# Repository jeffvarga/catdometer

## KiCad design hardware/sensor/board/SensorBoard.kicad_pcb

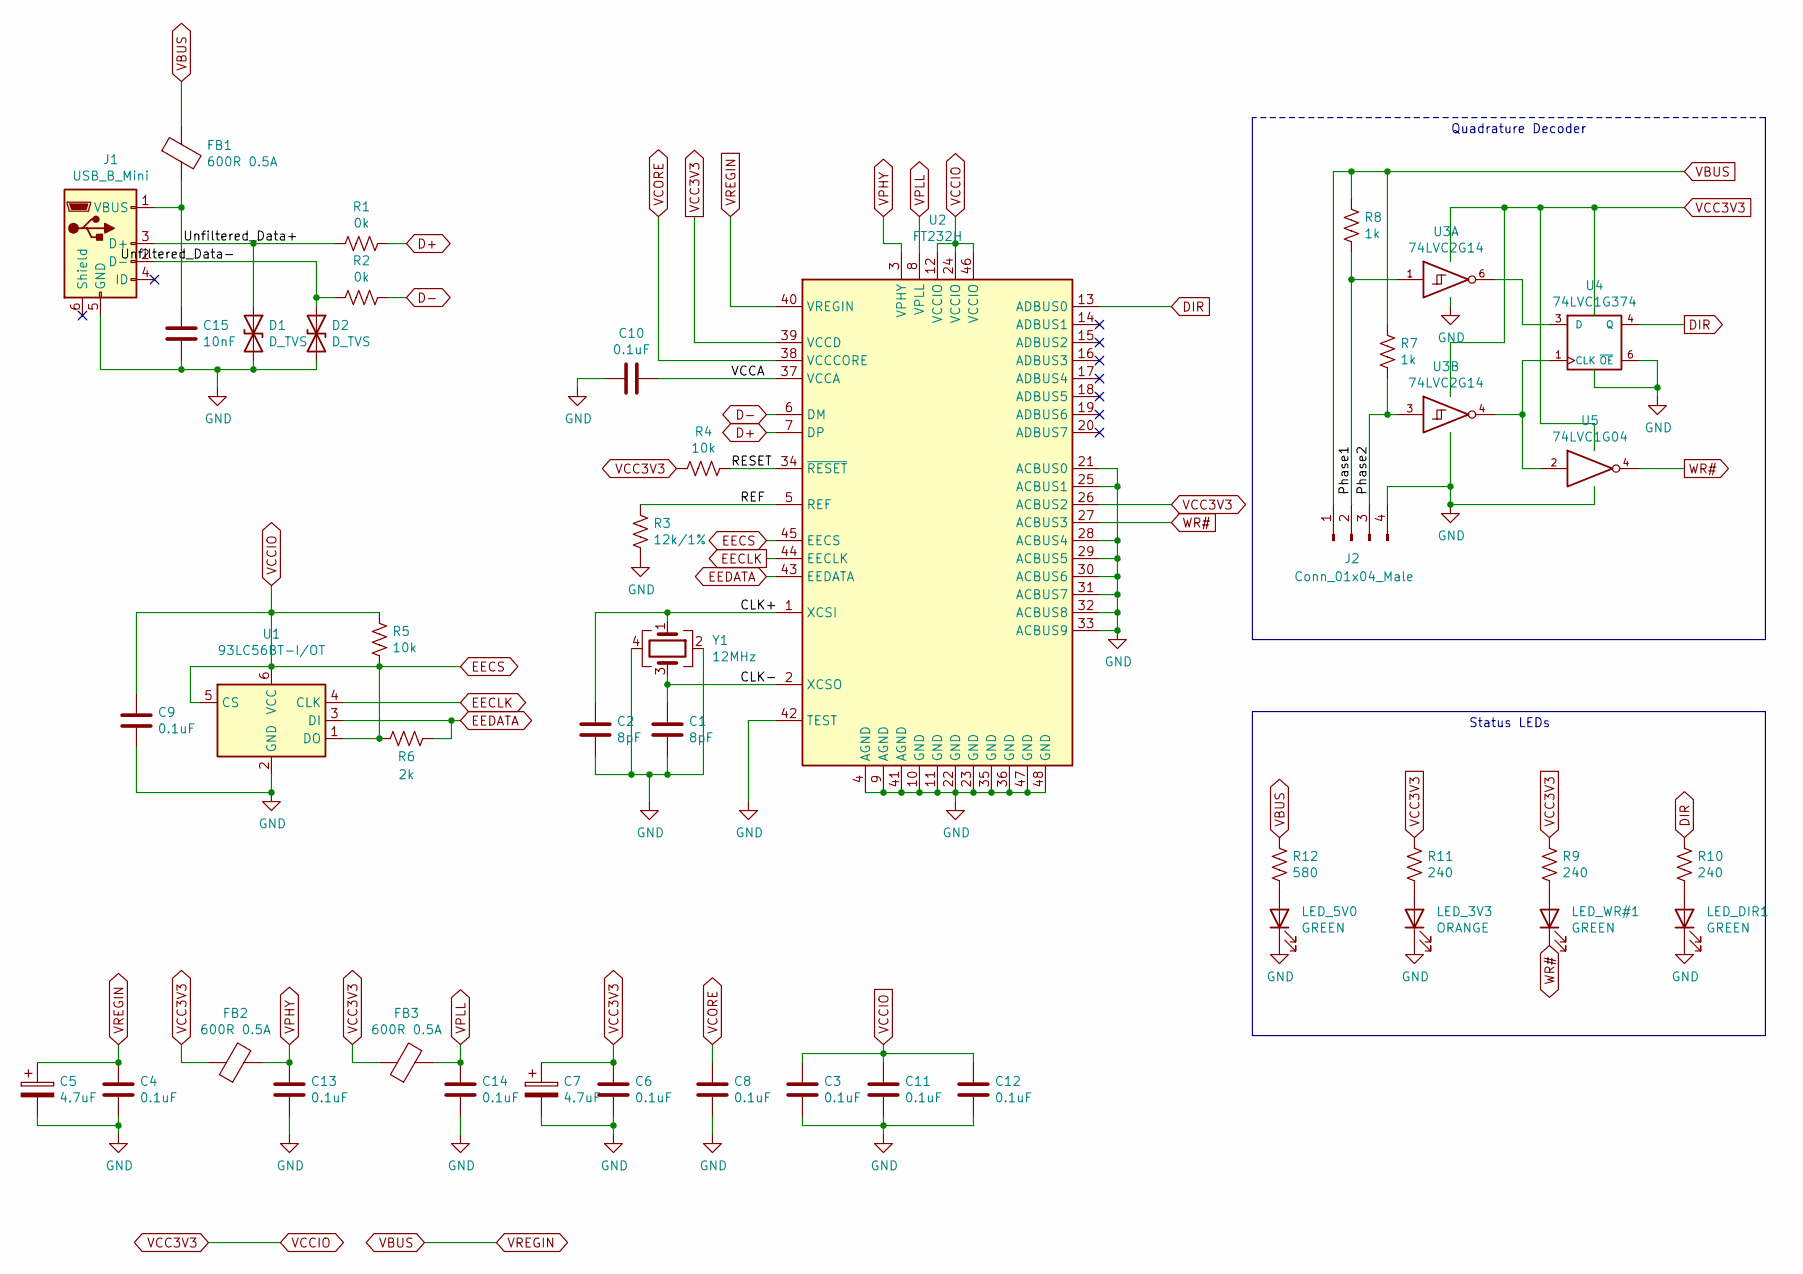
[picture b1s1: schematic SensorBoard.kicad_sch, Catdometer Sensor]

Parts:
C1, C2: 8pF; C_0603_1608Metric; Digikey Item CL10C270JB81PNC
C3, C4, C6, C8, C9, C10, C11, C12, C13, C14: 0.1uF; C_0603_1608Metric; Digikey Item CL10A104KA8NNNC
C5, C7: 4.7uF; C_0603_1608Metric; Digikey Item CL10A475KP8NNNC‎
C15: 10nF; C_0603_1608Metric; Digikey Item CL10B103KB8NNNC
D1, D2: D_TVS; D_0603_1608Metric; Digikey Item PGB1010603MR‎
FB1, FB2, FB3: 600R 0.5A; L_0603_1608Metric; Digikey Item BLM18AG601SN1D‎
J1: USB_B_Mini; USB_Mini-B_Wuerth_65100516121_Horizontal; Digikey Item ‎65100516121‎
J2: Conn_01x04_Male; PinHeader_1x04_P2.54mm_Vertical
LED_3V3: ORANGE; LED_0603_1608Metric
LED_5V0: GREEN; LED_0603_1608Metric
LED_DIR1: GREEN; LED_0603_1608Metric
LED_WR#1: GREEN; LED_0603_1608Metric
R1, R2: 0k; R_0603_1608Metric; Digikey Item ERJ-3GEY0R00V
R3: 12k/1%; R_0603_1608Metric; Digikey Item ERJ-PA3F1202V
R4, R5: 10k; R_0603_1608Metric; Digikey Item ERJ-PA3J103V
R6: 2k; R_0603_1608Metric; Digikey Item ‎ERJ-PA3J202V‎
R7, R8: 1k; R_0603_1608Metric; Digikey Item ERJ-PA3J102V
R9, R10: 240; R_0603_1608Metric; Digikey Item ERJ-PA3J102V
R11: 240; R_0603_1608Metric
R12: 580; R_0603_1608Metric
U1: 93LC56BT-I/OT; SOT-23-6
U2: FT232H; LQFP-48_7x7mm_P0.5mm
U3: 74LVC2G14; SOT-23-6
U4: 74LVC1G374; SOT-23-6
U5: 74LVC1G04; SOT-23-5
Y1: 12MHz; Crystal_SMD_2520-4Pin_2.5x2.0mm; Digikey Item ABM10-167-12.000MHZ-T3

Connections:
/CLK+: C2.1, U2.1 (XCSI), Y1.1
/CLK-: C1.1, U2.2 (XCSO), Y1.3
/Phase1: J2.2, R8.2, U3.1
/Phase2: J2.3, R7.2, U3.3
/REF: R3.1, U2.5 (REF)
/RESET: R4.1, U2.34 (~RESET)
/Unfiltered_Data+: D1.1 (A1), J1.3 (D+), R1.2
/Unfiltered_Data-: D2.1 (A1), J1.2 (D-), R2.2
/VCCA: C10.1, U2.37 (VCCA)
D+: R1.1, U2.7 (DP)
D-: R2.1, U2.6 (DM)
DIR: R10.1, U2.13 (ADBUS0), U4.4 (Q)
EECLK: U1.4 (CLK), U2.44 (EECLK)
EEDATA: R6.1, U1.3 (DI), U2.43 (EEDATA)
GND: C1.2, C2.2, C3.2, C4.2, C5.2, C6.2, C7.2, C8.2, C9.2, C10.2, C11.2, C12.2, C13.2, C14.2, C15.2, D1.2 (A2), D2.2 (A2), J1.5 (GND), J2.4, LED_3V3.1 (K), LED_5V0.1 (K), LED_DIR1.1 (K), R3.2, U1.2 (GND), U2.4 (AGND), U2.9 (AGND), U2.10 (GND), U2.11 (GND), U2.21 (ACBUS0), U2.22 (GND), U2.23 (GND), U2.25 (ACBUS1), U2.28 (ACBUS4), U2.29 (ACBUS5), U2.30 (ACBUS6), U2.31 (ACBUS7), U2.32 (ACBUS8), U2.33 (ACBUS9), U2.35 (GND), U2.36 (GND), U2.41 (AGND), U2.42 (TEST), U2.47 (GND), U2.48 (GND), U3.2 (GND), U4.2 (GND), U4.6 (~OE), U5.3 (GND), Y1.2, Y1.4
unnamed: C15.1, FB1.2, J1.1 (VBUS)
unnamed: LED_3V3.2 (A), R11.2
unnamed: LED_5V0.2 (A), R12.2
unnamed: LED_DIR1.2 (A), R10.2
unnamed: LED_WR#1.2 (A), R9.2
unnamed: U3.4, U4.1 (CLK), U5.2
unnamed: U3.6, U4.3 (D)
VBUS: C4.1, C5.1, FB1.1, J2.1, R7.1, R8.1, R12.1, U2.40 (VREGIN)
VCORE: C8.1, U2.38 (VCCCORE)
VPHY: C13.1, FB2.2, U2.3 (VPHY)
VPLL: C14.1, FB3.2, U2.8 (VPLL)
WR#: LED_WR#1.1 (K), U2.27 (ACBUS3), U5.4

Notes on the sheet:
Status LEDs
Quadrature Decoder

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
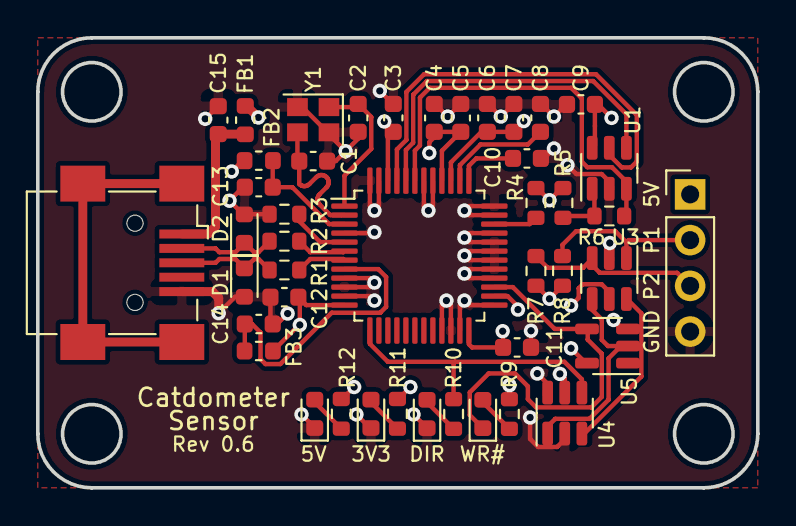
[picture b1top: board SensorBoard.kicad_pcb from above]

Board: 4 copper layers, 40.0 x 25.0 mm, 44 parts (0 on the bottom side), 30 nets.

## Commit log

2020-08-09 Create LICENSE
2020-08-09 Moving source files
2020-08-09 Refactoring code into modules
2020-08-11 Major refactor of libraries, arguing with python import semantics.
2020-08-11 Uploading correct version of service with path to real script
2020-08-28 Hey, I'm learning Tk! Using the proper packers for the job and reducing complexity of layout.
2020-08-28 Abstracting the speedometer circle drawing code into a base and derived classes to change the look.
2020-09-01 Change the default inactive tick style to dark gray
2020-09-01 Encapsulate some anonymous tuples in collections.namedtuple wrappers. Clean up some of the math for the DottedSpeedometer.
2020-09-02 Missing line break at end of file
2020-09-02 Moar colors
2020-09-02 Updating DottedSpeedometer to use named colors
2020-09-02 Refactoring Rect, Point into its own Geometry module. Adding a few helper functions to Rect like width/height.
2020-09-02 Rename of Speedometer (Base, Dashed, Dotted) to Gauge to reduce confusion and better represent what the class is doing.
2020-09-03 requirements.txt
2020-09-08 Initial Oracle skeleton
2021-01-28 Initial commit of sensor board KiCad files
2021-02-17 0603 Component attempt 1
2021-02-19 Layout from scratch
2021-02-21 Rev 0.5
    Added power planes galore, put bypass caps closer to UM232H
2021-02-22 Rev 0.5
    Added a debug LED, changed to crosshair reliefs on layer 1 ground plane
2021-02-24 A much needed .gitignore
    Ignoring KiCad cache files
2021-02-24 Fixing planes and debug LED
    Fixing some planes, via off of the debug LED
2021-03-06 Added power status LEDs
    Rev'd board to 0.6, added power status LEDs for 5V and 3V3 rails to help debug
2021-03-07 Board relayout
    Some relayout of the southern and eastern side of the board, addition of DIR LED, moving WR down to be with the rest.
2021-03-08 Reordering of resistors
2021-03-11 Fixing crystal caps
    Matching caps to crystal - 8pF
2021-03-11 Replacing decoder Schmitt IC
    Replacing LVC2G17 (Dual Schmitt Trigger Input Buffers) with LVC2G14 (Dual Schmitt Inverter)
2022-06-10 Updating to KiCad 6.0
    Updating schematic to KiCad 6.0, cleaning up some cache files.
